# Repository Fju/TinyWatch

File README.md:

# AVRist-watch

A DIY project that involves an ATmega328p that controlls a small monochrome OLED display powered by a chargable LiPo battery - or in short: a digital wrist watch.

## Features

- **Real Time Clock**: An IC keeps track of the current date and time even if the display and microcontroller is turned off.

- **Li-Po battery management**: The board features a charge controller that allows charging the battery via Micro USB. Another IC protects the battery from over-charging and over-discharging.

- **OLED-Display**: A monochrome 128x64 pixel OLED display is used to show the current time.

- **Energy Efficiency**: After displaying the current time for a couple of seconds the display turns off and the microcontroller enters a sleep mode. This saves battery power.

## Images

## Schematic

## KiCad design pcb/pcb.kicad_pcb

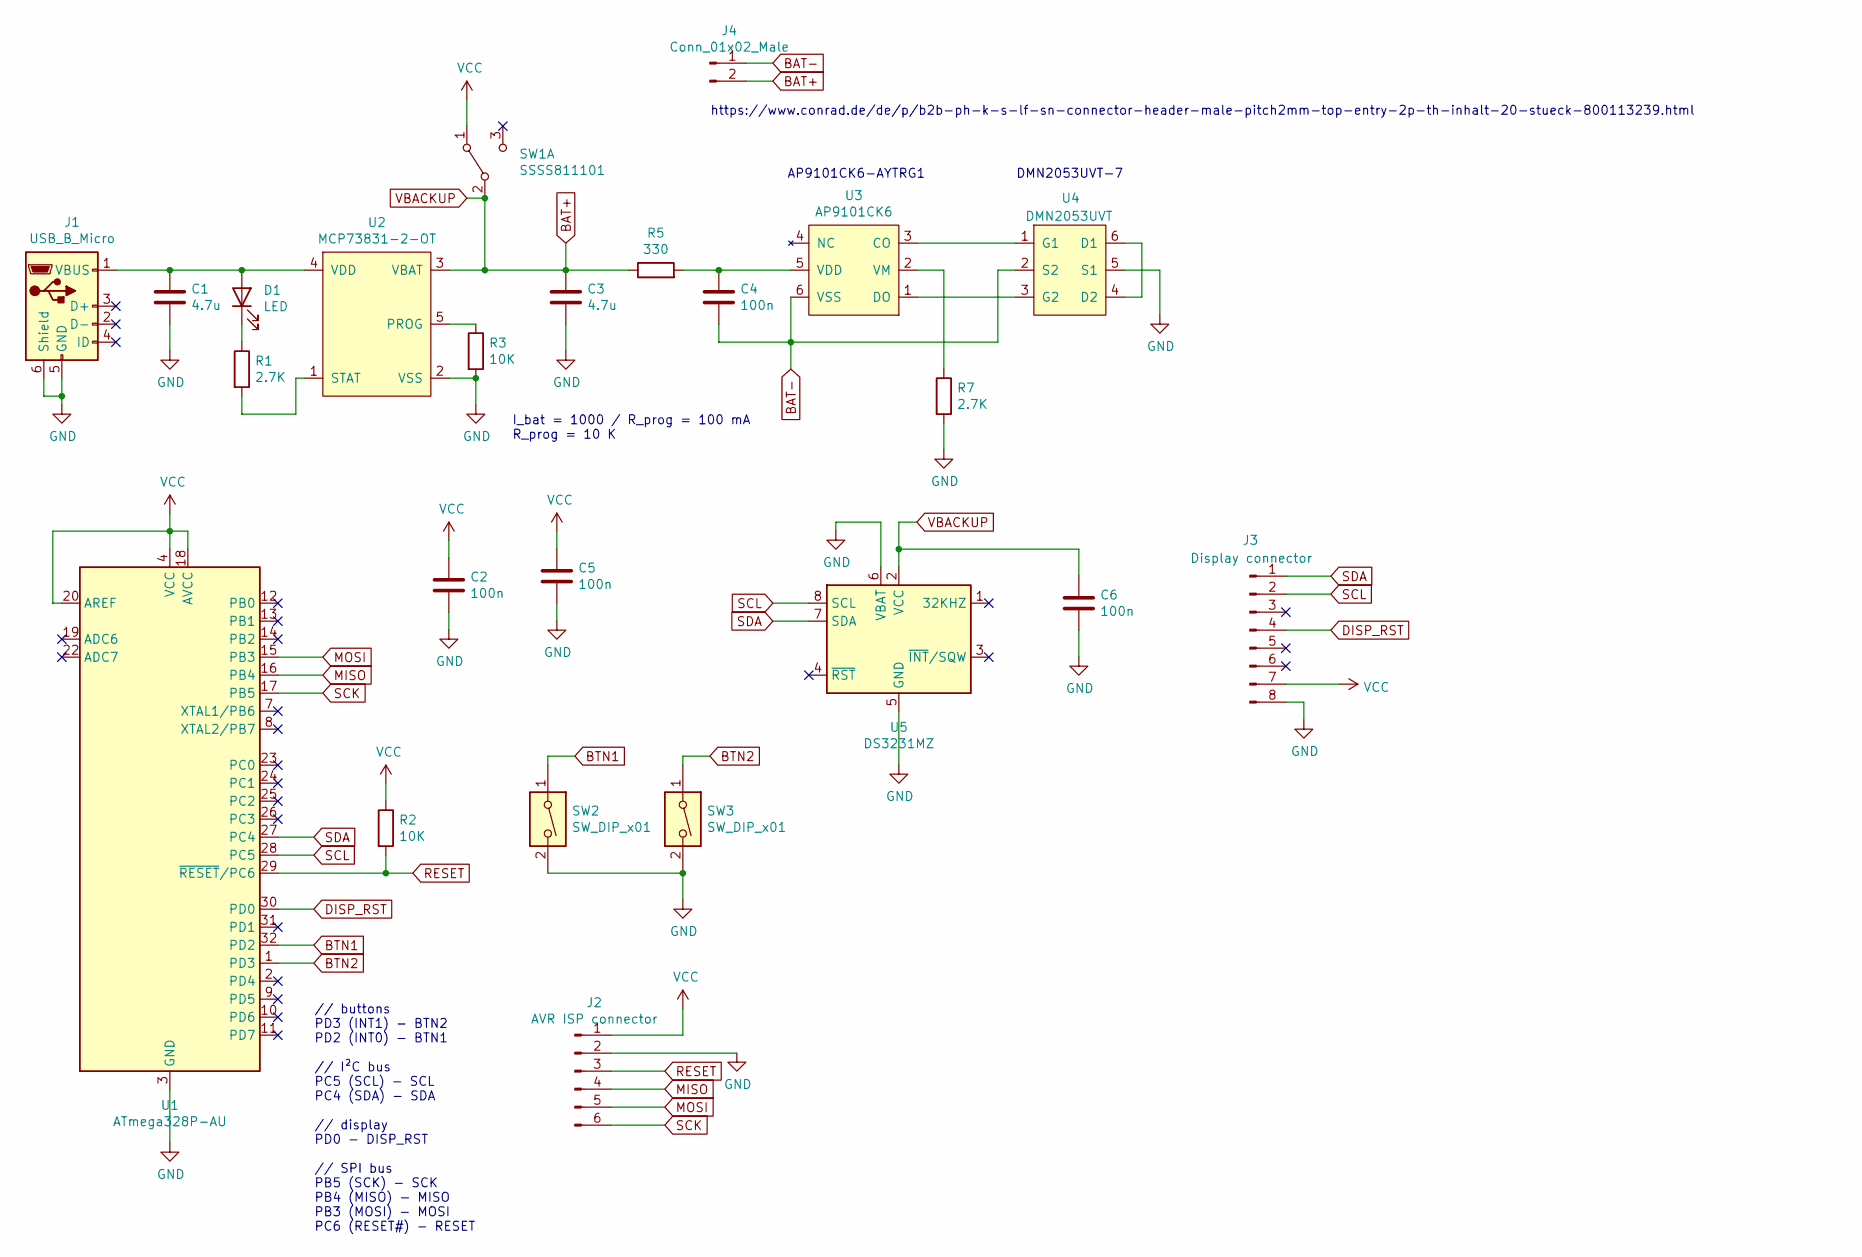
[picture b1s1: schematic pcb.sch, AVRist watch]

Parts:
C1, C3: 4.7u; C_0603_1608Metric
C2, C4, C5, C6: 100n; C_0603_1608Metric
D1: LED; LED_0805_2012Metric
J1: USB_B_Micro; USB_B_micro
J2: AVR ISP connector; CONN_AVR_ISP_SMD
J3: Display connector; PinHeader_1x08_P2.54mm_Vertical
J4: Conn_01x02_Male; JST_PH_B2B-PH-K_1x02_P2.00mm_Vertical
R1, R7: 2.7K; R_0603_1608Metric
R2, R3: 10K; R_0603_1608Metric
R5: 330; R_0603_1608Metric
SW1: SSSS811101
SW2, SW3: SW_DIP_x01; TL3340_SMT
U1: ATmega328P-AU; TQFP-32_7x7mm_P0.8mm
U2: MCP73831-2-OT; MCP73831_SOT-23
U3: AP9101CK6; AP9101C_SOT-25
U4: DMN2053UVT; DMN2053UVT_TSOT-26
U5: DS3231MZ; SOIC-8_3.9x4.9mm_P1.27mm

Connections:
BAT+: C3.1, C6.1, J4.2, R5.1, SW1.2 (B), U2.3 (VBAT), U5.2 (VCC)
BAT-: C4.2, J4.1, U3.6 (VSS), U4.2 (S2)
BTN1: SW2.1, U1.32 (PD2)
BTN2: SW3.1, U1.1 (PD3)
DISP_RST: J3.4, U1.30 (PD0)
GND: C1.2, C2.2, C3.2, C5.2, C6.2, J1.5 (GND), J1.6 (Shield), J2.2, J3.8, R3.2, R7.2, SW2.2, SW3.2, U1.3 (GND), U1.5 (GND), U1.21 (GND), U2.2 (VSS), U4.5 (S1), U5.5 (GND), U5.6 (VBAT)
MISO: J2.4, U1.16 (PB4)
MOSI: J2.5, U1.15 (PB3)
unnamed: C1.1, D1.2 (A), J1.1 (VBUS), U2.4 (VDD)
unnamed: C4.1, R5.2, U3.5 (VDD)
unnamed: D1.1 (K), R1.1
unnamed: R1.2, U2.1 (STAT)
unnamed: R3.1, U2.5 (PROG)
unnamed: R7.1, U3.2 (VM)
unnamed: U3.1 (DO), U4.3 (G2)
unnamed: U3.3 (CO), U4.1 (G1)
unnamed: U4.4 (D2), U4.6 (D1)
RESET: J2.3, R2.2, U1.29 (~RESET~/PC6)
SCK: J2.6, U1.17 (PB5)
SCL: J3.2, U1.28 (PC5), U5.8 (SCL)
SDA: J3.1, U1.27 (PC4), U5.7 (SDA)
VCC: C2.1, C5.1, J2.1, J3.7, R2.1, SW1.1 (A), U1.4 (VCC), U1.6 (VCC), U1.18 (AVCC), U1.20 (AREF)

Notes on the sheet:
I_bat = 1000 / R_prog = 100 mA R_prog = 10 K
// buttons PD3 (INT1) - BTN2 PD2 (INT0) - BTN1 // I²C bus PC5 (SCL) - SCL PC4 (SDA) - SDA // display PD0 - DISP_RST // SPI bus PB5 (SCK) - SCK PB4 (MISO) - MISO PB3 (MOSI) - MOSI PC6 (RESET#) - RESET
AP9101CK6-AYTRG1
DMN2053UVT-7
https://www.conrad.de/de/p/b2b-ph-k-s-lf-sn-connector-header-male-pitch2mm-top-entry-2p-th-inhalt-20-stueck-800113239.html

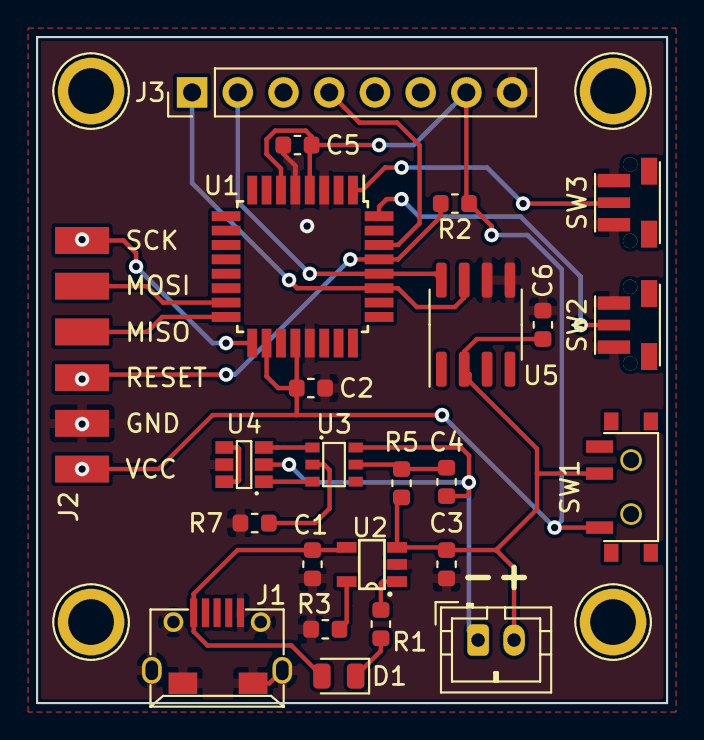
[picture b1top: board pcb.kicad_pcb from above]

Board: 2 copper layers, 35.0 x 37.0 mm, 24 parts (0 on the bottom side), 22 nets.

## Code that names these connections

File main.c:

#include <avr/io.h>
#include <avr/power.h>
#include <avr/sleep.h>
#include <avr/interrupt.h>

#include "screen.h"
#include "i2c_master.h"
#include "fonts.h"
#include "clock.h"

#include <util/delay.h>

enum state_t {
	S_TIME,			// display time
	S_MENU_TIME,	// set time (hours and minutes)
	S_MENU_DATE,	// set date (day and month)
	S_MENU_YEAR		// set year
};

int main() {
	// set all I/O to outputs to save some energy, except the following:
	// INT0 (PD2), INT1 (PD3), SCL (PC5), SDA (PC4)
    DDRB = 0xFF;
    DDRC |= ~((1 << PC5) | (1 << PC4));
    DDRD |= ~((1 << PD2) | (1 << PD3));

	// active pull-up 
	PORTD |= (1 << PD2) | (1 << PD3);

	// turn off ADC
	ACSR = 0x80;

	// disable all components except TWI
	PRR |= ~(1 << PRTWI);

	// allocate memory for screen
	if (screen_begin()) while(1);

	// set interrupt enabled
	sei();


	enum state_t state;

	uint8_t btn1_state = 0;
	uint8_t btn2_state = 0;

	uint8_t hours = 0;
	uint8_t minutes = 0;
	uint8_t day = 0;
	uint8_t month = 0;
	uint8_t year = 0;

	uint8_t digit_selection = 0;

	uint8_t timeout = 0;

	// wake up/sleep loop
	while(1) {
		// two-wire interface needs to be resetted
		i2c_init();

		// turn on screen
		screen_on();

		state = S_TIME;
		timeout = 0;

		// display loop
		while (1) {
			// update state of button 1
			if (PIND & (1 << PD2)) {
				btn1_state = 0;
			} else if (btn1_state < 32) {
			   	++btn1_state;
			}
			
			// update state of button 2 
			if (PIND & (1 << PD3)) {
				btn2_state = 0;
			} else if (btn2_state < 32) {
				++btn2_state;
			}

			switch (state) {
				case S_TIME:
					// obtain time from RTC
					minutes = get_minutes();
					hours = get_hours();

					// display time
					screen_draw_character(numbers_bitmap, hours / 10, NUMBERS_CHAR_HEIGHT, NUMBERS_CHAR_WIDTH, 4, 15, 0);
					screen_draw_character(numbers_bitmap, hours % 10, NUMBERS_CHAR_HEIGHT, NUMBERS_CHAR_WIDTH, 28, 15, 0);
					screen_draw_character(numbers_bitmap, 10, NUMBERS_CHAR_HEIGHT, NUMBERS_CHAR_WIDTH, 52, 15, 0);
					screen_draw_character(numbers_bitmap, minutes / 10, NUMBERS_CHAR_HEIGHT, NUMBERS_CHAR_WIDTH, 78, 15, 0);
					screen_draw_character(numbers_bitmap, minutes % 10, NUMBERS_CHAR_HEIGHT, NUMBERS_CHAR_WIDTH, 102, 15, 0);

					++timeout;

					// detect long press
					if (btn1_state > 20) {
						// switch state
						state = S_MENU_TIME;
						screen_clear();
						// don't timeout when not in state S_TIME
						timeout = 0;
						// get day, month and year once
						day = get_date();
						month = get_month();
						year = get_year();
					}
					break;
				case S_MENU_TIME:
					// draw header ("hh:mm")
					screen_draw_character(character_bitmap, 4, TEXT_CHAR_HEIGHT, TEXT_CHAR_WIDTH, 24, 1, 0);
					screen_draw_character(character_bitmap, 4, TEXT_CHAR_HEIGHT, TEXT_CHAR_WIDTH, 40, 1, 0);
					screen_draw_character(character_bitmap, 5, TEXT_CHAR_HEIGHT, TEXT_CHAR_WIDTH, 56, 1, 0);
					screen_draw_character(character_bitmap, 3, TEXT_CHAR_HEIGHT, TEXT_CHAR_WIDTH, 72, 1, 0);
					screen_draw_character(character_bitmap, 3, TEXT_CHAR_HEIGHT, TEXT_CHAR_WIDTH, 88, 1, 0);

					screen_draw_character(numbers_bitmap, hours / 10, NUMBERS_CHAR_HEIGHT, NUMBERS_CHAR_WIDTH, 4, 30, digit_selection == 0 ? 0xFF : 0);
					screen_draw_character(numbers_bitmap, hours % 10, NUMBERS_CHAR_HEIGHT, NUMBERS_CHAR_WIDTH, 28, 30, digit_selection == 1 ? 0xFF : 0);
					screen_draw_character(numbers_bitmap, 10, NUMBERS_CHAR_HEIGHT, NUMBERS_CHAR_WIDTH, 52, 30, 0);
					screen_draw_character(numbers_bitmap, minutes / 10, NUMBERS_CHAR_HEIGHT, NUMBERS_CHAR_WIDTH, 78, 30, digit_selection == 2 ? 0xFF : 0);
					screen_draw_character(numbers_bitmap, minutes % 10, NUMBERS_CHAR_HEIGHT, NUMBERS_CHAR_WIDTH, 102, 30, digit_selection == 3 ? 0xFF : 0);

					if (btn1_state == 1) {
						++digit_selection;

						if (digit_selection == 4) {
							// update time
							set_hours(hours);
							set_minutes(minutes);

							// switch state
							state = S_MENU_DATE;
							screen_clear();
							digit_selection = 0;
						}
					}

					if (btn2_state == 1) {
						if (digit_selection == 0) hours += 10;
						else if (digit_selection == 1) hours += 1;
						else if (digit_selection == 2) minutes += 10;
						else if (digit_selection == 3) minutes += 1;

						if (hours > 23) hours = 0;
						if (minutes > 59) minutes = 0;
					}
					break;
				case S_MENU_DATE:
					// draw header ("DD MM")
					screen_draw_character(character_bitmap, 1, TEXT_CHAR_HEIGHT, TEXT_CHAR_WIDTH, 24, 1, 0);
					screen_draw_character(character_bitmap, 1, TEXT_CHAR_HEIGHT, TEXT_CHAR_WIDTH, 40, 1, 0);
					screen_draw_character(character_bitmap, 2, TEXT_CHAR_HEIGHT, TEXT_CHAR_WIDTH, 72, 1, 0);
					screen_draw_character(character_bitmap, 2, TEXT_CHAR_HEIGHT, TEXT_CHAR_WIDTH, 88, 1, 0);

					screen_draw_character(numbers_bitmap, day / 10, NUMBERS_CHAR_HEIGHT, NUMBERS_CHAR_WIDTH, 4, 30, digit_selection == 0 ? 0xFF : 0);
					screen_draw_character(numbers_bitmap, day % 10, NUMBERS_CHAR_HEIGHT, NUMBERS_CHAR_WIDTH, 28, 30, digit_selection == 1 ? 0xFF : 0);

					screen_draw_character(numbers_bitmap, month / 10, NUMBERS_CHAR_HEIGHT, NUMBERS_CHAR_WIDTH, 78, 30, digit_selection == 2 ? 0xFF : 0);
					screen_draw_character(numbers_bitmap, month % 10, NUMBERS_CHAR_HEIGHT, NUMBERS_CHAR_WIDTH, 102, 30, digit_selection == 3 ? 0xFF : 0);

					if (btn1_state == 1) {
						++digit_selection;

						if (digit_selection == 4) {
							// update date
							set_date(day);
							set_month(month);

							// switch state
							state = S_MENU_YEAR;
							screen_clear();
							digit_selection = 0;
						}
					}

					if (btn2_state == 1) {
						if (digit_selection == 0) day += 10;
						else if (digit_selection == 1) day += 1;
						else if (digit_selection == 2) month += 10;
						else if (digit_selection == 3) month += 1;

						if (day > 31) day = 1;
						if (month > 12) month = 1;
					}
					break;
				case S_MENU_YEAR:
					// draw header ("YYYY")
					screen_draw_character(character_bitmap, 0, TEXT_CHAR_HEIGHT, TEXT_CHAR_WIDTH, 32, 1, 0);
					screen_draw_character(character_bitmap, 0, TEXT_CHAR_HEIGHT, TEXT_CHAR_WIDTH, 48, 1, 0);
					screen_draw_character(character_bitmap, 0, TEXT_CHAR_HEIGHT, TEXT_CHAR_WIDTH, 64, 1, 0);
					screen_draw_character(character_bitmap, 0, TEXT_CHAR_HEIGHT, TEXT_CHAR_WIDTH, 80, 1, 0);
					
					// draw digits of year
					screen_draw_character(numbers_bitmap, 2, NUMBERS_CHAR_HEIGHT, NUMBERS_CHAR_WIDTH, 16, 30, 0);
					screen_draw_character(numbers_bitmap, 0, NUMBERS_CHAR_HEIGHT, NUMBERS_CHAR_WIDTH, 40, 30, 0);
					screen_draw_character(numbers_bitmap, year / 10, NUMBERS_CHAR_HEIGHT, NUMBERS_CHAR_WIDTH, 64, 30, digit_selection == 0 ? 0xFF : 0);
					screen_draw_character(numbers_bitmap, year % 10, NUMBERS_CHAR_HEIGHT, NUMBERS_CHAR_WIDTH, 86, 30, digit_selection == 1 ? 0xFF : 0);
					
					if (btn1_state == 1) {
						++digit_selection;

						if (digit_selection == 2) {
							// update year
							set_year(year);

							// switch state
							state = S_TIME;
							screen_clear();
							digit_selection = 0;
						}
					}
				
					if (btn2_state == 1) {
						if (digit_selection == 0) year += 10;
						else if (digit_selection == 1) year += 1;

						if (year > 99) year = 0;
					}
					break;
			}

			// refresh screen
			screen_display();
			_delay_ms(60);

			if (timeout > 50) {
				// leave loop, go to sleep
				break;
			}
		}	

		// turn off screen
		screen_off();

		// enable INT0 and INT1
		EIMSK |= (1 << INT1) | (1 << INT0);

		// sleep in power down mode
		set_sleep_mode(SLEEP_MODE_PWR_DOWN);
        sleep_mode();

		// wake up here, disable interrupts
		EIMSK &= ~((1 << INT1) | (1 << INT0));
	}
}

// these interrupt routines MUST exists but can be empty
ISR(INT0_vect) {
}

ISR(INT1_vect) {
}

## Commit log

2018-11-17 Library for custom parts
    Eagle hasn't got the BQ32002 and the MCP73831/2 required for this project. So I created a library that includes these parts. All dimensions and pin names were adopted from the official datasheets.
2018-11-17 Corrected unit for custom parts' footprints
    I messed up the units when I created the library for the custom parts (used milli-inch instead of millimeters).
2018-11-18 Added CC4V-T1A oscillator to library
2018-11-19 Added laying capacitor and C++ source code
    The code files originate from adafruits SSD1306 library and were modified for the use of the ATTiny84. I will add more details about this in the next commit.
2018-11-21 Added .ino for Arduino IDE
2020-02-18 Complete rewrite
2020-02-18 Added `bin` directory
2020-02-18 Changed title in README
2020-02-18 Added schematic to `docs`
2020-02-23 Added screen library
2020-02-23 DO NOT use ATmega168 !!
2020-03-04 Added fuses configuration and explanation
2020-03-04 Added clock module
2020-03-07 Improved screen and clock module
2020-03-07 Added python script to generate font bitmaps
2020-03-08 Designed schematic using KiCAD
2020-03-08 Improved schematic
2020-03-11 Decimal font test
2020-03-16 Updated schematic and added gitignore for KiCAD files
2020-03-17 Added datasheets and push button footprint
2020-03-17 Updated footprints and schematic
2020-03-29 Finalized PCB layout
2020-04-25 Finalized schematic and PCB layout
2020-05-02 Changed TL3340 footprint
2020-05-21 Pull-up for INT0 and INT1, display reset pin
2020-05-21 Fixed MISO/MOSI mistake in PCB and schematic
2020-05-21 Added schematic to README
2020-05-23 Added menu for setting date and time
2020-05-23 Added two pictures and 3D printed mounts
2020-05-26 Fixed setting hours
2021-03-19 Bump pillow from 7.0.0 to 8.1.1 in /fonts
    Bumps [pillow](https://github.com/python-pillow/Pillow) from 7.0.0 to 8.1.1.
    - [Release notes](https://github.com/python-pillow/Pillow/releases)
    - [Changelog](https://github.com/python-pillow/Pillow/blob/master/CHANGES.rst)
    - [Commits](https://github.com/python-pillow/Pillow/compare/7.0.0...8.1.1)
2021-06-08 Bump pillow from 7.0.0 to 8.2.0 in /fonts
    Bumps [pillow](https://github.com/python-pillow/Pillow) from 7.0.0 to 8.2.0.
    - [Release notes](https://github.com/python-pillow/Pillow/releases)
    - [Changelog](https://github.com/python-pillow/Pillow/blob/master/CHANGES.rst)
    - [Commits](https://github.com/python-pillow/Pillow/compare/7.0.0...8.2.0)
    ---
    updated-dependencies:
